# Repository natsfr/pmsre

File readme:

============================
== Powerfull Motor System ==
== Rocks Everything       ==
============================

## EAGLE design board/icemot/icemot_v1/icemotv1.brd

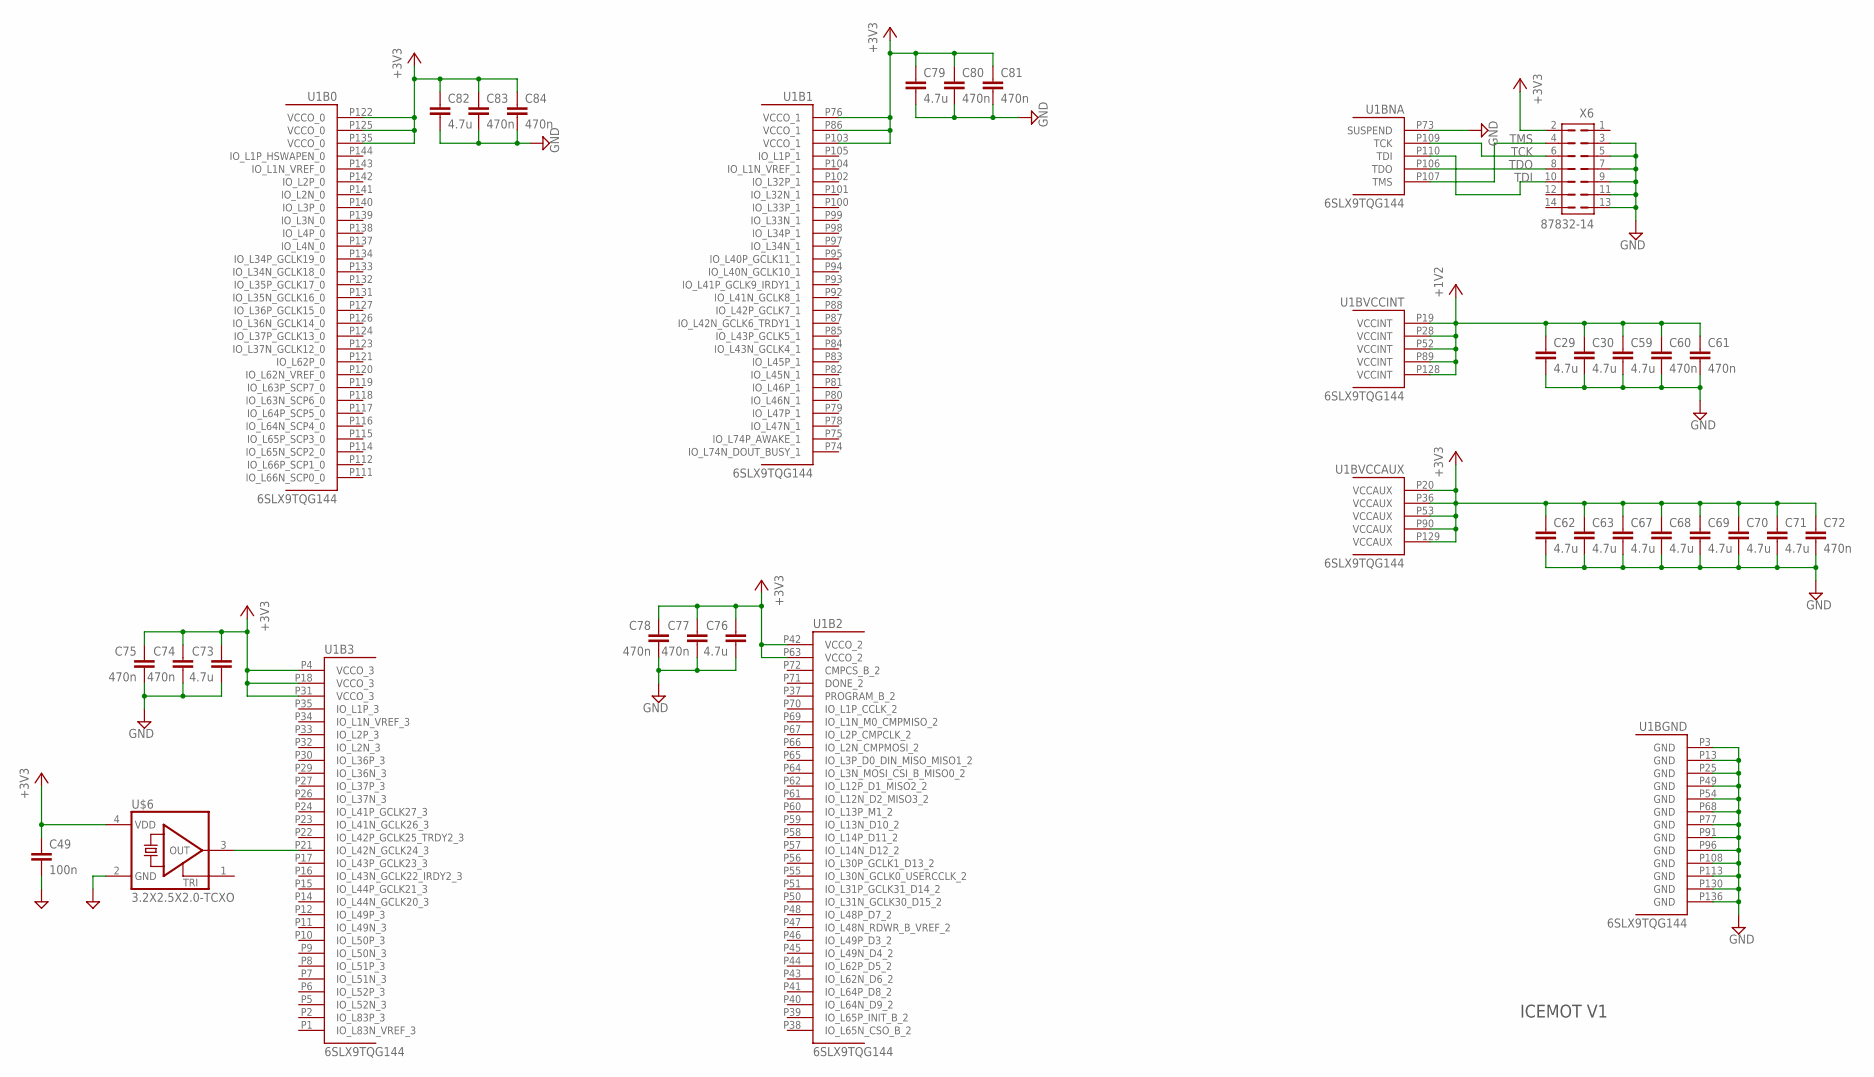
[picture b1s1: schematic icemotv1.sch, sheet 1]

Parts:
C29, C30, C59, C62, C63, C67, C68, C69, C70, C71, C73, C76, C79, C82: 4.7u; C0603
C49: 100n; R0603
C60, C61, C72, C74, C75, C77, C78, C80, C81, C83, C84: 470n; C0603
U1: 6SLX9TQG144; TQ144
U$6: 3.2X2.5X2.0-TCXO
X6: 87832-14

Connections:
+1V2: C29.1, C30.1, C59.1, C60.1, C61.1
+3V3: C49.1, C62.1, C63.1, C67.1, C68.1, C69.1, C70.1, C71.1, C72.1, C73.1, C74.1, C75.1, C76.1, C77.1, C78.1, C79.1, C80.1, C81.1, C82.1, C83.1, C84.1, U1.P20 (VCCAUX), U1.P36 (VCCAUX), U1.P53 (VCCAUX), U1.P90 (VCCAUX), U1.P129 (VCCAUX), U$6.4 (VDD), X6.2; also elsewhere on the board
GND: C29.2, C30.2, C49.2, C59.2, C60.2, C61.2, C62.2, C63.2, C67.2, C68.2, C69.2, C70.2, C71.2, C72.2, C73.2, C74.2, C75.2, C76.2, C77.2, C78.2, C79.2, C80.2, C81.2, C82.2, C83.2, C84.2, U1.P3 (GND), U1.P13 (GND), U1.P25 (GND), U1.P49 (GND), U1.P54 (GND), U1.P68 (GND), U1.P73 (SUSPEND), U1.P77 (GND), U1.P91 (GND), U1.P96 (GND), U1.P108 (GND), U1.P113 (GND), U1.P130 (GND), U1.P136 (GND), U$6.2 (GND), X6.3, X6.5, X6.7, X6.9, X6.11, X6.13; also elsewhere on the board
unnamed: U1.P21 (IO_L42N_GCLK24_3), U$6.3 (OUT)
TCK: U1.P109 (TCK), X6.6
TDI: U1.P110 (TDI), X6.10
TDO: U1.P106 (TDO), X6.8
TMS: U1.P107 (TMS), X6.4

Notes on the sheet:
ICEMOT V1

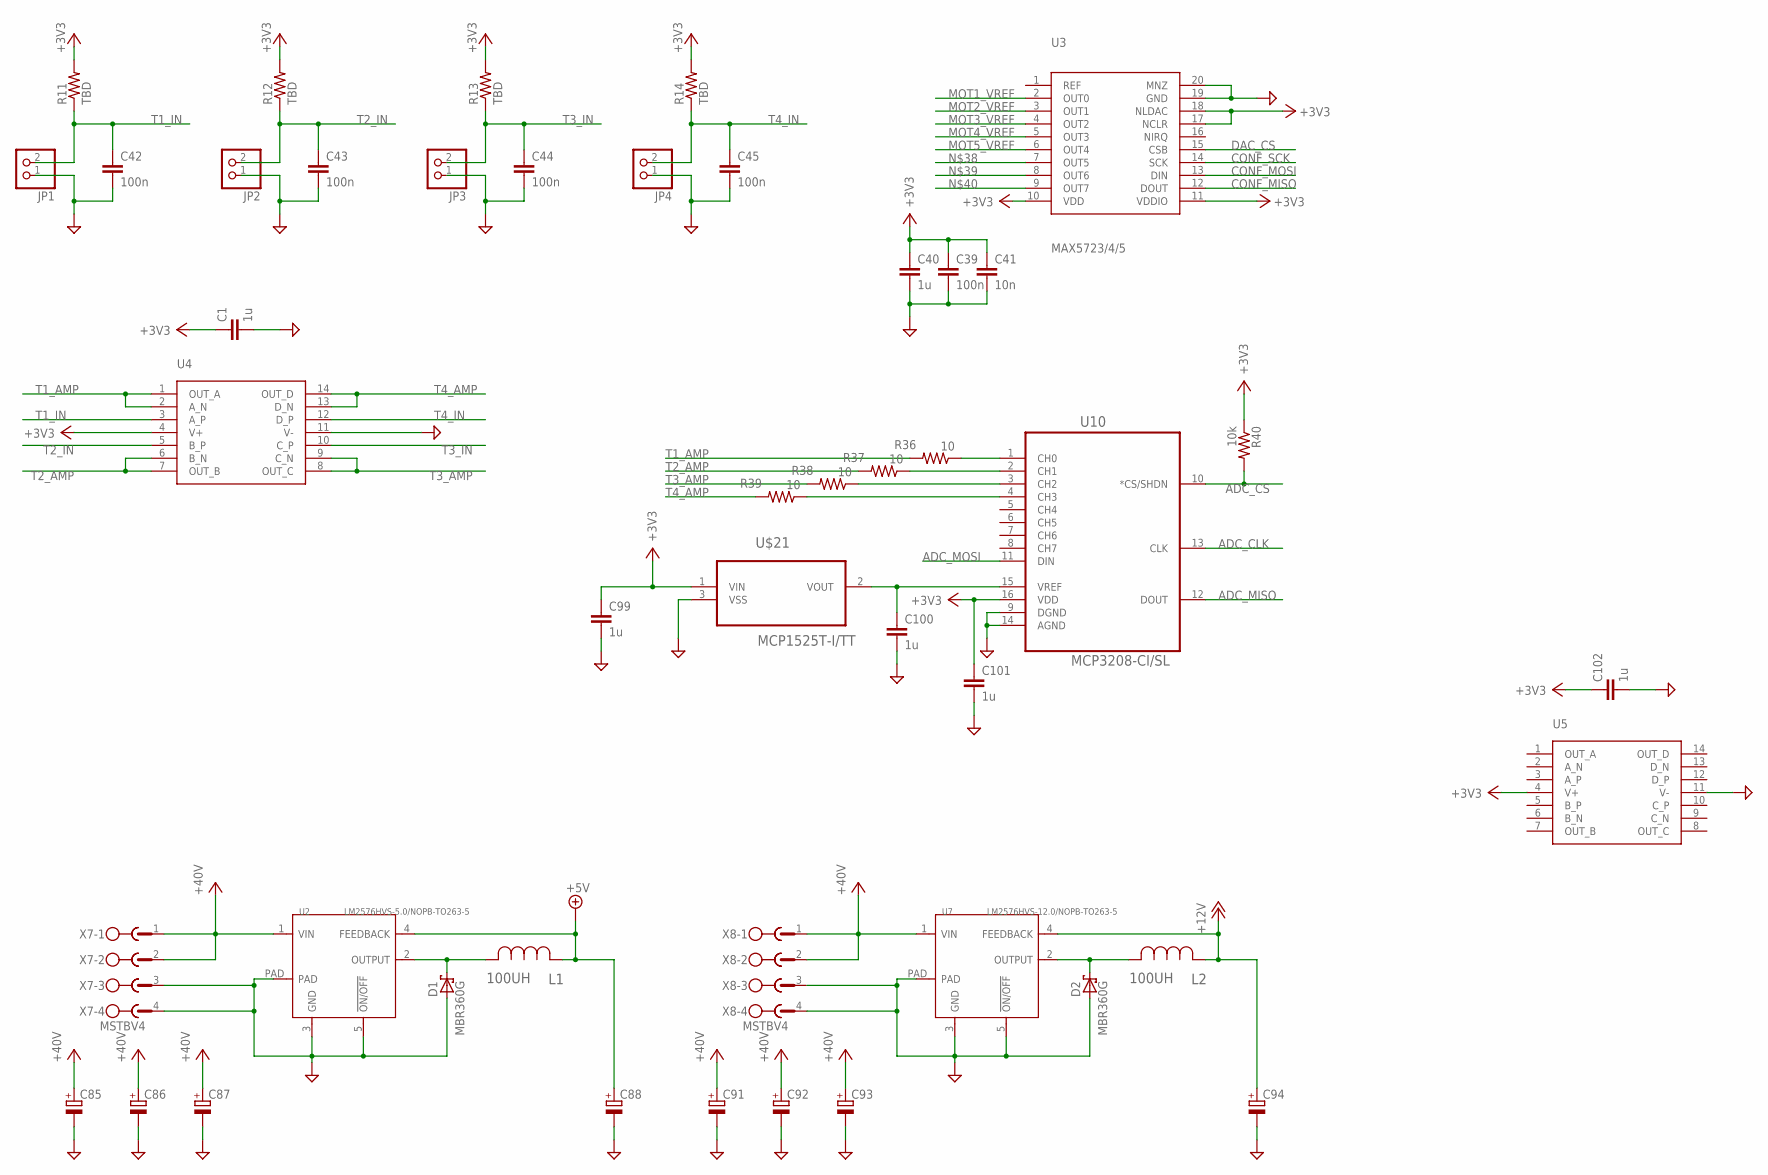
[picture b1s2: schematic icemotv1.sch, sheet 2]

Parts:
C1, C40, C99, C100, C101, C102: 1u; R0603
C39, C42, C43, C44, C45: 100n; R0603
C41: 10n; R0603
C85, C86, C87, C88, C91, C92, C93, C94: CPOL-EUE5-10.5; E5-10,5
D1, D2: MBR360G; DO201T15
JP1, JP2, JP3, JP4: PINHD-1X2; 1X02
L1, L2: 100UH; IND_ELC18B
R11, R12, R13, R14: TBD; R0603
R36, R37, R38, R39: 10; R0603
R40: 10k; R0603
U2: LM2576HVS-5.0/NOPB-TO263-5; TO-263-5
U3: MAX5723/4/5; TSSOP20-0.65-6.5X4.4MM
U4, U5: TLV4379; TSSOP14-0.65-5X4.4MM
U7: LM2576HVS-12.0/NOPB-TO263-5; TO-263-5
U10: MCP3208-CI/SL; SOIC127P600X175-16N
U$21: MCP1525T-I/TT; SOT96P237X112-3N
X7, X8: MSTBV4

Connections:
+3V3: C1.1, C39.1, C40.1, C41.1, C99.1, C101.1, C102.1, R11.2, R12.2, R13.2, R14.2, R40.1, U3.10 (VDD), U3.11 (VDDIO), U3.17 (NCLR), U3.18 (NLDAC), U4.4 (V+), U10.16 (VDD), U$21.1 (VIN); also elsewhere on the board
+5V: C88.+, L1.1, U2.4 (FEEDBACK)
+12V: C94.+, L2.1, U7.4 (FEEDBACK); also elsewhere on the board
+40V: C85.+, C86.+, C87.+, C91.+, C92.+, C93.+, U2.1 (VIN), U7.1 (VIN), X7.1, X7.2, X8.1, X8.2; also elsewhere on the board
ADC_CLK: U10.13 (CLK)
ADC_CS: R40.2, U10.10 (*CS/SHDN)
ADC_MISO: U10.12 (DOUT)
ADC_MOSI: U10.11 (DIN)
CONF_MISO: U3.12 (DOUT)
CONF_MOSI: U3.13 (DIN)
CONF_SCK: U3.14 (SCK)
DAC_CS: U3.15 (CSB)
GND: C1.2, C39.2, C40.2, C41.2, C42.2, C43.2, C44.2, C45.2, C85.-, C86.-, C87.-, C88.-, C91.-, C92.-, C93.-, C94.-, C99.2, C100.2, C101.2, C102.2, D1.A, D2.A, JP1.1, JP2.1, JP3.1, JP4.1, U2.3 (GND), U2.5 (!ON/OFF), U2.PAD, U3.19 (GND), U3.20 (MNZ), U4.11 (V-), U7.3 (GND), U7.5 (!ON/OFF), U7.PAD, U10.9 (DGND), U10.14 (AGND), U$21.3 (VSS), X7.3, X7.4, X8.3, X8.4; also elsewhere on the board
MOT1_VREF: U3.2 (OUT0); also elsewhere on the board
MOT2_VREF: U3.3 (OUT1); also elsewhere on the board
MOT3_VREF: U3.4 (OUT2); also elsewhere on the board
MOT4_VREF: U3.5 (OUT3); also elsewhere on the board
MOT5_VREF: U3.6 (OUT4); also elsewhere on the board
unnamed: D1.C, L1.2, U2.2 (OUTPUT)
unnamed: D2.C, L2.2, U7.2 (OUTPUT)
unnamed: C100.1, U10.15 (VREF), U$21.2 (VOUT)
unnamed: R36.1, U10.1 (CH0)
unnamed: R37.1, U10.2 (CH1)
unnamed: R38.1, U10.3 (CH2)
unnamed: R39.1, U10.4 (CH3)
T1_AMP: R36.2, U4.1 (OUT_A), U4.2 (A_N)
T1_IN: C42.1, JP1.2, R11.1, U4.3 (A_P)
T2_AMP: R37.2, U4.6 (B_N), U4.7 (OUT_B)
T2_IN: C43.1, JP2.2, R12.1, U4.5 (B_P)
T3_AMP: R38.2, U4.8 (OUT_C), U4.9 (C_N)
T3_IN: C44.1, JP3.2, R13.1, U4.10 (C_P)
T4_AMP: R39.2, U4.13 (D_N), U4.14 (OUT_D)
T4_IN: C45.1, JP4.2, R14.1, U4.12 (D_P)
V+: U5.4 (V+)
V-: U5.11 (V-)

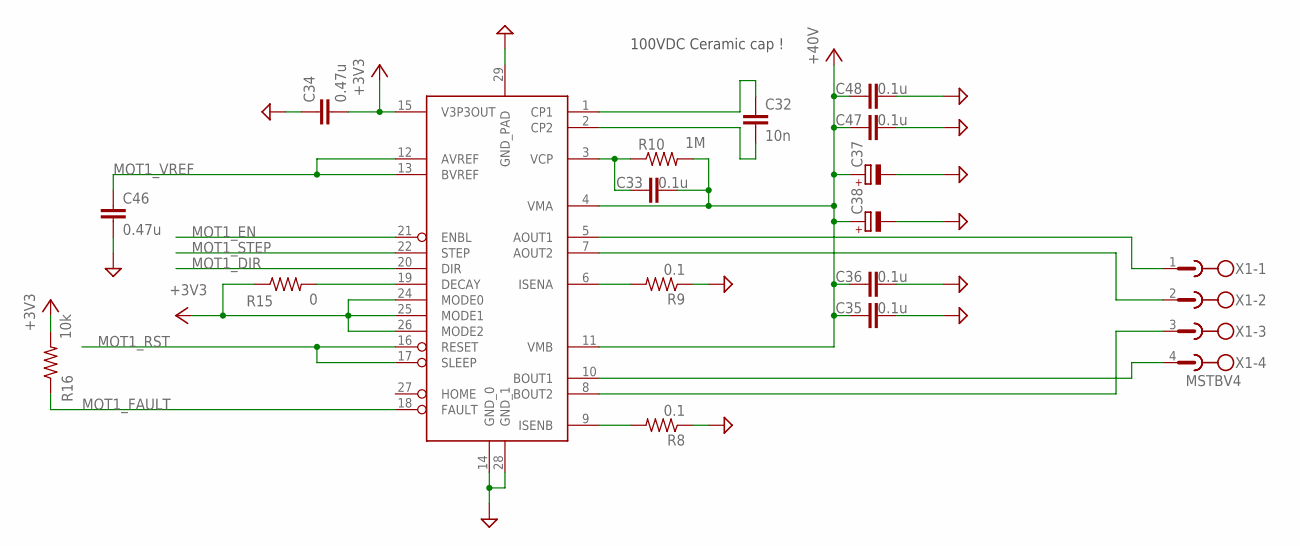
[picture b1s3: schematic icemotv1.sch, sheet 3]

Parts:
C32: 10n; R0603
C33, C35, C36, C47, C48: 0.1u; R0603
C34, C46: 0.47u; R0603
C37, C38: CPOL-EUE5-5; E5-5
R8, R9: 0.1; R1206
R10: 1M; R0603
R15: 0; R0603
R16: 10k; R0603
U$4: DRV8825PWP; TSSOP-28
X1: MSTBV4

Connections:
+3V3: C34.2, R15.1, R16.2, U$4.15 (V3P3OUT), U$4.24 (MODE0), U$4.25 (MODE1), U$4.26 (MODE2); also elsewhere on the board
+40V: C33.2, C35.1, C36.1, C37.+, C38.+, C47.1, C48.1, R10.2, U$4.4 (VMA), U$4.11 (VMB); also elsewhere on the board
GND: C34.1, C35.2, C36.2, C37.-, C38.-, C46.2, C47.2, C48.2, R8.1, R9.1, U$4.14 (GND_0), U$4.28 (GND_1), U$4.29 (GND_PAD); also elsewhere on the board
MOT1_DIR: U$4.20 (DIR)
MOT1_EN: U$4.21 (ENBL)
MOT1_FAULT: R16.1, U$4.18 (FAULT)
MOT1_RST: U$4.16 (RESET), U$4.17 (SLEEP)
MOT1_STEP: U$4.22 (STEP)
MOT1_VREF: C46.1, U$4.12 (AVREF), U$4.13 (BVREF); also elsewhere on the board
unnamed: R9.2, U$4.6 (ISENA)
unnamed: R8.2, U$4.9 (ISENB)
unnamed: C32.1, U$4.1 (CP1)
unnamed: C32.2, U$4.2 (CP2)
unnamed: C33.1, R10.1, U$4.3 (VCP)
unnamed: R15.2, U$4.19 (DECAY)
unnamed: U$4.5 (AOUT1), X1.1
unnamed: U$4.7 (AOUT2), X1.2
unnamed: U$4.8 (BOUT2), X1.3
unnamed: U$4.10 (BOUT1), X1.4

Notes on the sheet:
100VDC Ceramic cap !

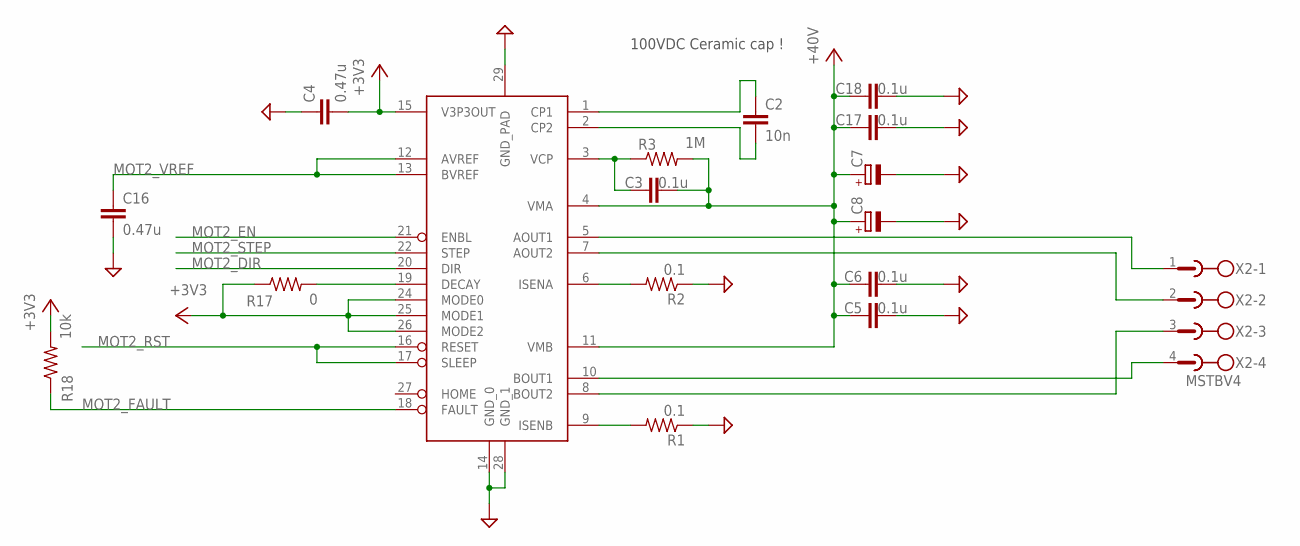
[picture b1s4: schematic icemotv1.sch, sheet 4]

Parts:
C2: 10n; R0603
C3, C5, C6, C17, C18: 0.1u; R0603
C4, C16: 0.47u; R0603
C7, C8: CPOL-EUE5-5; E5-5
R1, R2: 0.1; R1206
R3: 1M; R0603
R17: 0; R0603
R18: 10k; R0603
U$1: DRV8825PWP; TSSOP-28
X2: MSTBV4

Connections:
+3V3: C4.2, R17.1, R18.2, U$1.15 (V3P3OUT), U$1.24 (MODE0), U$1.25 (MODE1), U$1.26 (MODE2); also elsewhere on the board
+40V: C3.2, C5.1, C6.1, C7.+, C8.+, C17.1, C18.1, R3.2, U$1.4 (VMA), U$1.11 (VMB); also elsewhere on the board
GND: C4.1, C5.2, C6.2, C7.-, C8.-, C16.2, C17.2, C18.2, R1.1, R2.1, U$1.14 (GND_0), U$1.28 (GND_1), U$1.29 (GND_PAD); also elsewhere on the board
MOT2_DIR: U$1.20 (DIR)
MOT2_EN: U$1.21 (ENBL)
MOT2_FAULT: R18.1, U$1.18 (FAULT)
MOT2_RST: U$1.16 (RESET), U$1.17 (SLEEP)
MOT2_STEP: U$1.22 (STEP)
MOT2_VREF: C16.1, U$1.12 (AVREF), U$1.13 (BVREF); also elsewhere on the board
unnamed: R2.2, U$1.6 (ISENA)
unnamed: R1.2, U$1.9 (ISENB)
unnamed: C2.1, U$1.1 (CP1)
unnamed: C2.2, U$1.2 (CP2)
unnamed: C3.1, R3.1, U$1.3 (VCP)
unnamed: U$1.5 (AOUT1), X2.1
unnamed: U$1.7 (AOUT2), X2.2
unnamed: U$1.8 (BOUT2), X2.3
unnamed: U$1.10 (BOUT1), X2.4
unnamed: R17.2, U$1.19 (DECAY)

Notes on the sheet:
100VDC Ceramic cap !

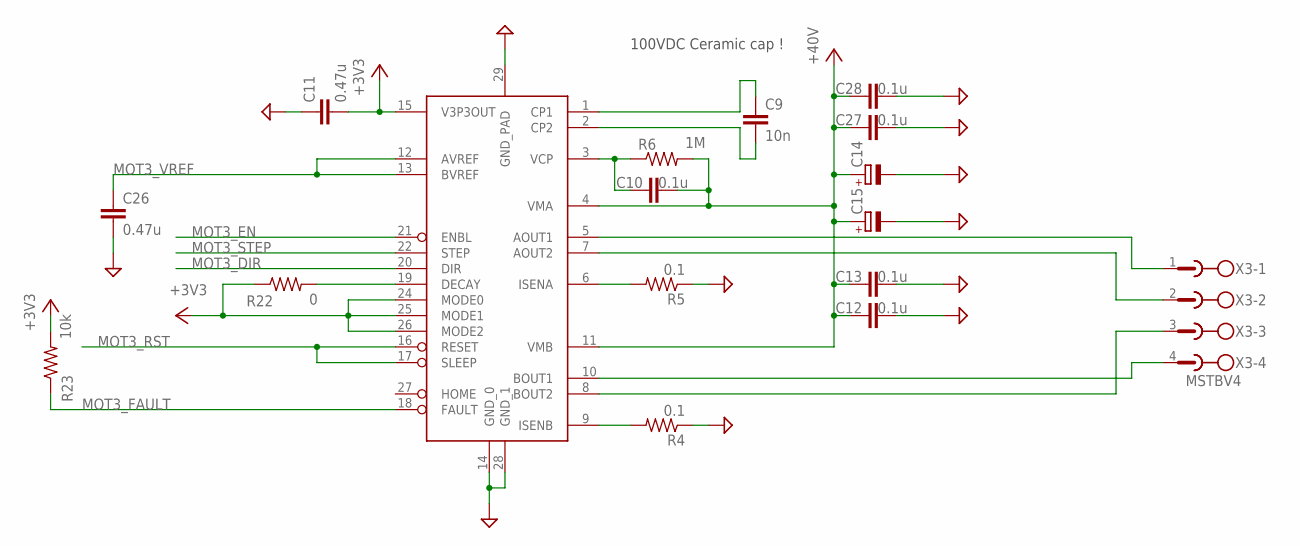
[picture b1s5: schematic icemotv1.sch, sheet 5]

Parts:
C9: 10n; R0603
C10, C12, C13, C27, C28: 0.1u; R0603
C11, C26: 0.47u; R0603
C14, C15: CPOL-EUE5-5; E5-5
R4, R5: 0.1; R1206
R6: 1M; R0603
R22: 0; R0603
R23: 10k; R0603
U$3: DRV8825PWP; TSSOP-28
X3: MSTBV4

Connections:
+3V3: C11.2, R22.1, R23.2, U$3.15 (V3P3OUT), U$3.24 (MODE0), U$3.25 (MODE1), U$3.26 (MODE2); also elsewhere on the board
+40V: C10.2, C12.1, C13.1, C14.+, C15.+, C27.1, C28.1, R6.2, U$3.4 (VMA), U$3.11 (VMB); also elsewhere on the board
GND: C11.1, C12.2, C13.2, C14.-, C15.-, C26.2, C27.2, C28.2, R4.1, R5.1, U$3.14 (GND_0), U$3.28 (GND_1), U$3.29 (GND_PAD); also elsewhere on the board
MOT3_DIR: U$3.20 (DIR)
MOT3_EN: U$3.21 (ENBL)
MOT3_FAULT: R23.1, U$3.18 (FAULT)
MOT3_RST: U$3.16 (RESET), U$3.17 (SLEEP)
MOT3_STEP: U$3.22 (STEP)
MOT3_VREF: C26.1, U$3.12 (AVREF), U$3.13 (BVREF); also elsewhere on the board
unnamed: R5.2, U$3.6 (ISENA)
unnamed: R4.2, U$3.9 (ISENB)
unnamed: C9.1, U$3.1 (CP1)
unnamed: C9.2, U$3.2 (CP2)
unnamed: C10.1, R6.1, U$3.3 (VCP)
unnamed: U$3.5 (AOUT1), X3.1
unnamed: U$3.7 (AOUT2), X3.2
unnamed: U$3.8 (BOUT2), X3.3
unnamed: U$3.10 (BOUT1), X3.4
unnamed: R22.2, U$3.19 (DECAY)

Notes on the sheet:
100VDC Ceramic cap !

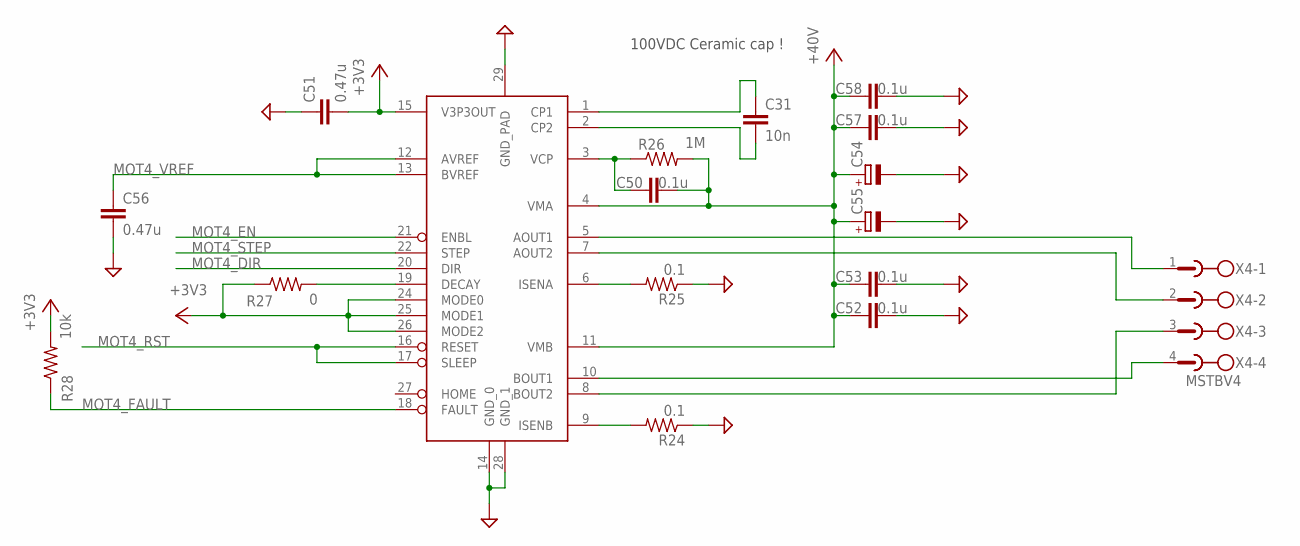
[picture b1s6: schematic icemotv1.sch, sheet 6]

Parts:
C31: 10n; R0603
C50, C52, C53, C57, C58: 0.1u; R0603
C51, C56: 0.47u; R0603
C54, C55: CPOL-EUE5-5; E5-5
R24, R25: 0.1; R1206
R26: 1M; R0603
R27: 0; R0603
R28: 10k; R0603
U$9: DRV8825PWP; TSSOP-28
X4: MSTBV4

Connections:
+3V3: C51.2, R27.1, R28.2, U$9.15 (V3P3OUT), U$9.24 (MODE0), U$9.25 (MODE1), U$9.26 (MODE2); also elsewhere on the board
+40V: C50.2, C52.1, C53.1, C54.+, C55.+, C57.1, C58.1, R26.2, U$9.4 (VMA), U$9.11 (VMB); also elsewhere on the board
GND: C51.1, C52.2, C53.2, C54.-, C55.-, C56.2, C57.2, C58.2, R24.1, R25.1, U$9.14 (GND_0), U$9.28 (GND_1), U$9.29 (GND_PAD); also elsewhere on the board
MOT4_DIR: U$9.20 (DIR)
MOT4_EN: U$9.21 (ENBL)
MOT4_FAULT: R28.1, U$9.18 (FAULT)
MOT4_RST: U$9.16 (RESET), U$9.17 (SLEEP)
MOT4_STEP: U$9.22 (STEP)
MOT4_VREF: C56.1, U$9.12 (AVREF), U$9.13 (BVREF); also elsewhere on the board
unnamed: R25.2, U$9.6 (ISENA)
unnamed: R24.2, U$9.9 (ISENB)
unnamed: C31.1, U$9.1 (CP1)
unnamed: C31.2, U$9.2 (CP2)
unnamed: C50.1, R26.1, U$9.3 (VCP)
unnamed: U$9.5 (AOUT1), X4.1
unnamed: U$9.7 (AOUT2), X4.2
unnamed: U$9.8 (BOUT2), X4.3
unnamed: U$9.10 (BOUT1), X4.4
unnamed: R27.2, U$9.19 (DECAY)

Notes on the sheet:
100VDC Ceramic cap !

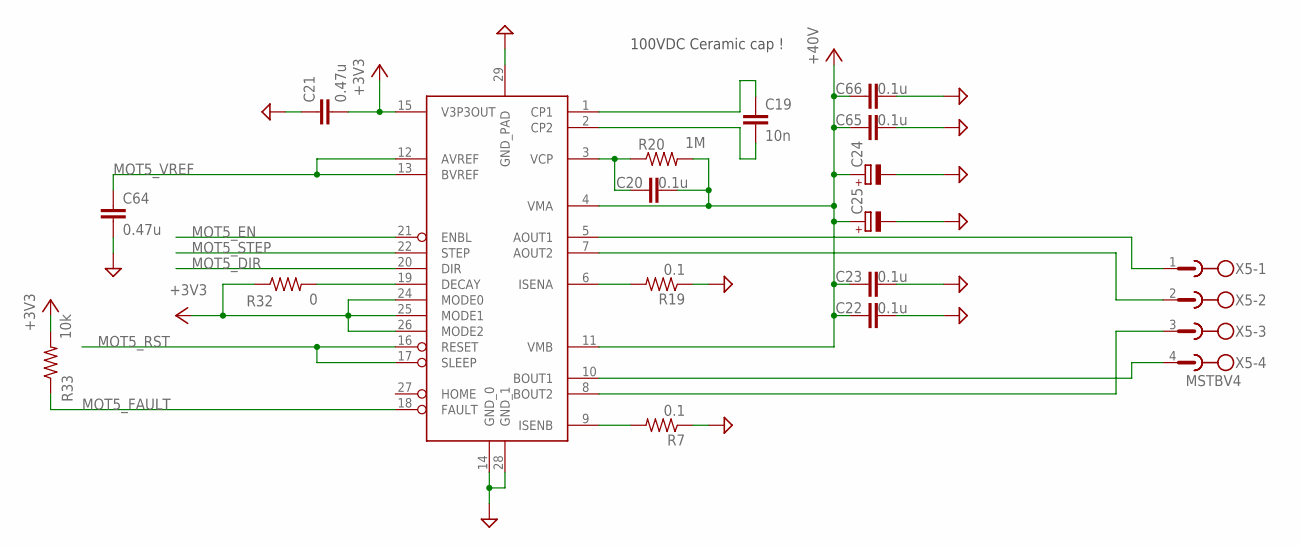
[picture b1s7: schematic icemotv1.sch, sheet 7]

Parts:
C19: 10n; R0603
C20, C22, C23, C65, C66: 0.1u; R0603
C21, C64: 0.47u; R0603
C24, C25: CPOL-EUE5-5; E5-5
R7, R19: 0.1; R1206
R20: 1M; R0603
R32: 0; R0603
R33: 10k; R0603
U$8: DRV8825PWP; TSSOP-28
X5: MSTBV4

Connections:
+3V3: C21.2, R32.1, R33.2, U$8.15 (V3P3OUT), U$8.24 (MODE0), U$8.25 (MODE1), U$8.26 (MODE2); also elsewhere on the board
+40V: C20.2, C22.1, C23.1, C24.+, C25.+, C65.1, C66.1, R20.2, U$8.4 (VMA), U$8.11 (VMB); also elsewhere on the board
GND: C21.1, C22.2, C23.2, C24.-, C25.-, C64.2, C65.2, C66.2, R7.1, R19.1, U$8.14 (GND_0), U$8.28 (GND_1), U$8.29 (GND_PAD); also elsewhere on the board
MOT5_DIR: U$8.20 (DIR)
MOT5_EN: U$8.21 (ENBL)
MOT5_FAULT: R33.1, U$8.18 (FAULT)
MOT5_RST: U$8.16 (RESET), U$8.17 (SLEEP)
MOT5_STEP: U$8.22 (STEP)
MOT5_VREF: C64.1, U$8.12 (AVREF), U$8.13 (BVREF); also elsewhere on the board
unnamed: R19.2, U$8.6 (ISENA)
unnamed: R7.2, U$8.9 (ISENB)
unnamed: C19.1, U$8.1 (CP1)
unnamed: C19.2, U$8.2 (CP2)
unnamed: C20.1, R20.1, U$8.3 (VCP)
unnamed: U$8.5 (AOUT1), X5.1
unnamed: U$8.7 (AOUT2), X5.2
unnamed: U$8.8 (BOUT2), X5.3
unnamed: U$8.10 (BOUT1), X5.4
unnamed: R32.2, U$8.19 (DECAY)

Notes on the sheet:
100VDC Ceramic cap !

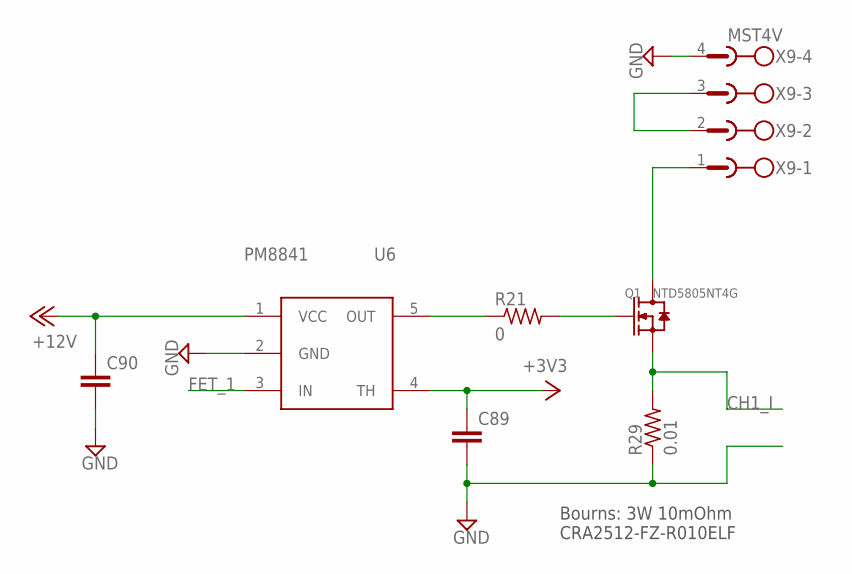
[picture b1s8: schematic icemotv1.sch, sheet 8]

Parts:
C89, C90: C-EUC0603; C0603
Q1: NTD5805NT4G; DPAK
R21: 0; R1206
R29: 0.01; R2512
U6: PM8841; SOT23-5
X9: MST4V; MSTBV4

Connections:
+3V3: C89.1, U6.4 (TH); also elsewhere on the board
+12V: C90.1, U6.1 (VCC); also elsewhere on the board
CH1_I: Q1.3 (S), R29.2
FET_1: U6.3 (IN)
GND: C89.2, C90.2, R29.1, U6.2 (GND), X9.4; also elsewhere on the board
unnamed: Q1.2 (D), X9.1
unnamed: R21.1, U6.5 (OUT)
unnamed: Q1.1 (G), R21.2
unnamed: X9.2, X9.3

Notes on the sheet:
Bourns: 3W 10mOhm CRA2512-FZ-R010ELF

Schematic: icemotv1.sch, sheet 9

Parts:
C95, C96: C-EUC0603; C0603
Q2: NTD5805NT4G; DPAK
R30: 0; R1206
R31: 0.01; R2512
U8: PM8841; SOT23-5
X10: MST4V; MSTBV4

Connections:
+3V3: C95.1, U8.4 (TH); also elsewhere on the board
+12V: C96.1, U8.1 (VCC); also elsewhere on the board
CH2_I: Q2.3 (S), R31.2
FET_2: U8.3 (IN)
GND: C95.2, C96.2, R31.1, U8.2 (GND), X10.4; also elsewhere on the board
unnamed: R30.1, U8.5 (OUT)
unnamed: Q2.1 (G), R30.2
unnamed: Q2.2 (D), X10.1
unnamed: X10.2, X10.3

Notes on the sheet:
Bourns: 3W 10mOhm CRA2512-FZ-R010ELF

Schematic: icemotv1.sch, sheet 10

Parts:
C97, C98: C-EUC0603; C0603
Q3: NTD5805NT4G; DPAK
R34: 0; R1206
R35: 0.01; R2512
U9: PM8841; SOT23-5
X11: MST4V; MSTBV4

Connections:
+3V3: C97.1, U9.4 (TH); also elsewhere on the board
+12V: C98.1, U9.1 (VCC); also elsewhere on the board
CH3_I: Q3.3 (S), R35.2
FET_3: U9.3 (IN)
GND: C97.2, C98.2, R35.1, U9.2 (GND), X11.4; also elsewhere on the board
unnamed: R34.1, U9.5 (OUT)
unnamed: Q3.1 (G), R34.2
unnamed: Q3.2 (D), X11.1
unnamed: X11.2, X11.3

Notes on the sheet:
Bourns: 3W 10mOhm CRA2512-FZ-R010ELF

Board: 2 copper layers, 181 parts (0 on the bottom side), 107 nets, no tracks yet.

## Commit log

2014-11-20 start xc3s200a schematic
2014-12-05 continue spartan 3 schematic
2014-12-05 done spartan 3a schematic
2014-12-06 added fpga configuration
2014-12-07 added 1.2V schematic
2014-12-29 prout
2015-01-04 added dac start routing
2015-01-04 placing USB and motor connector
2015-01-06 Changed motor connector => 4 layers board
2015-01-10 boring commit message
2015-01-11 routing first driver
2015-01-12 routed 3 drivers
2015-01-12 RER B blablabla
2015-01-13 routed 12->3.3v miss mezzanine header
2015-01-13 added lib resistors
2015-01-14 blabla vroum vroum
2015-01-18 added decoupling capacitor + 4 pin connector
2015-01-18 routing crap
2015-01-20 added fixing hole - capacitor on vref
2015-01-21 footprint cleanup
2015-01-22 Footprint assign cleanup done
2015-01-24 blabla
2015-01-25 adding mezzanine connector
2015-01-26 jtag con & serial
2015-01-27 routing adc connector + SPI | removed mode selector
2015-01-29 routing adc input
2015-01-30 pouet
2015-01-30 added an other 7 point connector
2015-01-31 last commit before gerber checking
2015-02-01 Finished silkscreen time to sleep
2015-02-01 added fpga/arm/driver doc
2015-02-01 added output D for dac
2015-02-01 first gerber release
2015-02-02 cleaned part: now use kicad-component repository
2015-02-02 clean autosave file
2015-02-04 added .gitignore
2015-02-07 corrected library reference
2015-03-03 converted PCB to Kicad 2014
2015-03-12 changing capacitor and correcting some net
2015-03-12 removed old component traces + migrated pcbnew file
2015-03-16 starting BOM
2015-03-29 correction + BOM
2015-06-04 hard: working board by nats
2015-06-06 soft: add basic software files
2015-11-23 mutekh: working spi
2015-11-28 shell: motor current and fpga loading
2015-12-06 Working RAM + SPI: Tested S3AN StarterKit
2015-12-13 1st working fpga code, ok for 3 motors
2015-12-13 added pullups on motor fault
2016-01-23 new spi register set
2016-04-13 added irq and cs line
2016-04-24 improved hdl & updated mutekh application
2016-11-26 starting ICE based board
2016-11-27 adding decoupling and usb connector
2016-11-27 added xtal, usb to be checked
2016-11-27 starting ICE schematic
2016-11-27 need to add interface to motor
2016-11-27 added oscillator, clock to be routed on GBin
2016-11-27 added res on decay
2016-12-17 remove ICE40 and EFM32, add a S6 LX9
2016-12-19 added ADC DCDC and copied 5 drv8825
2017-03-08 added a 12V rail, Power Mosfet
2017-04-02 added ADC and opamp for mosfet
